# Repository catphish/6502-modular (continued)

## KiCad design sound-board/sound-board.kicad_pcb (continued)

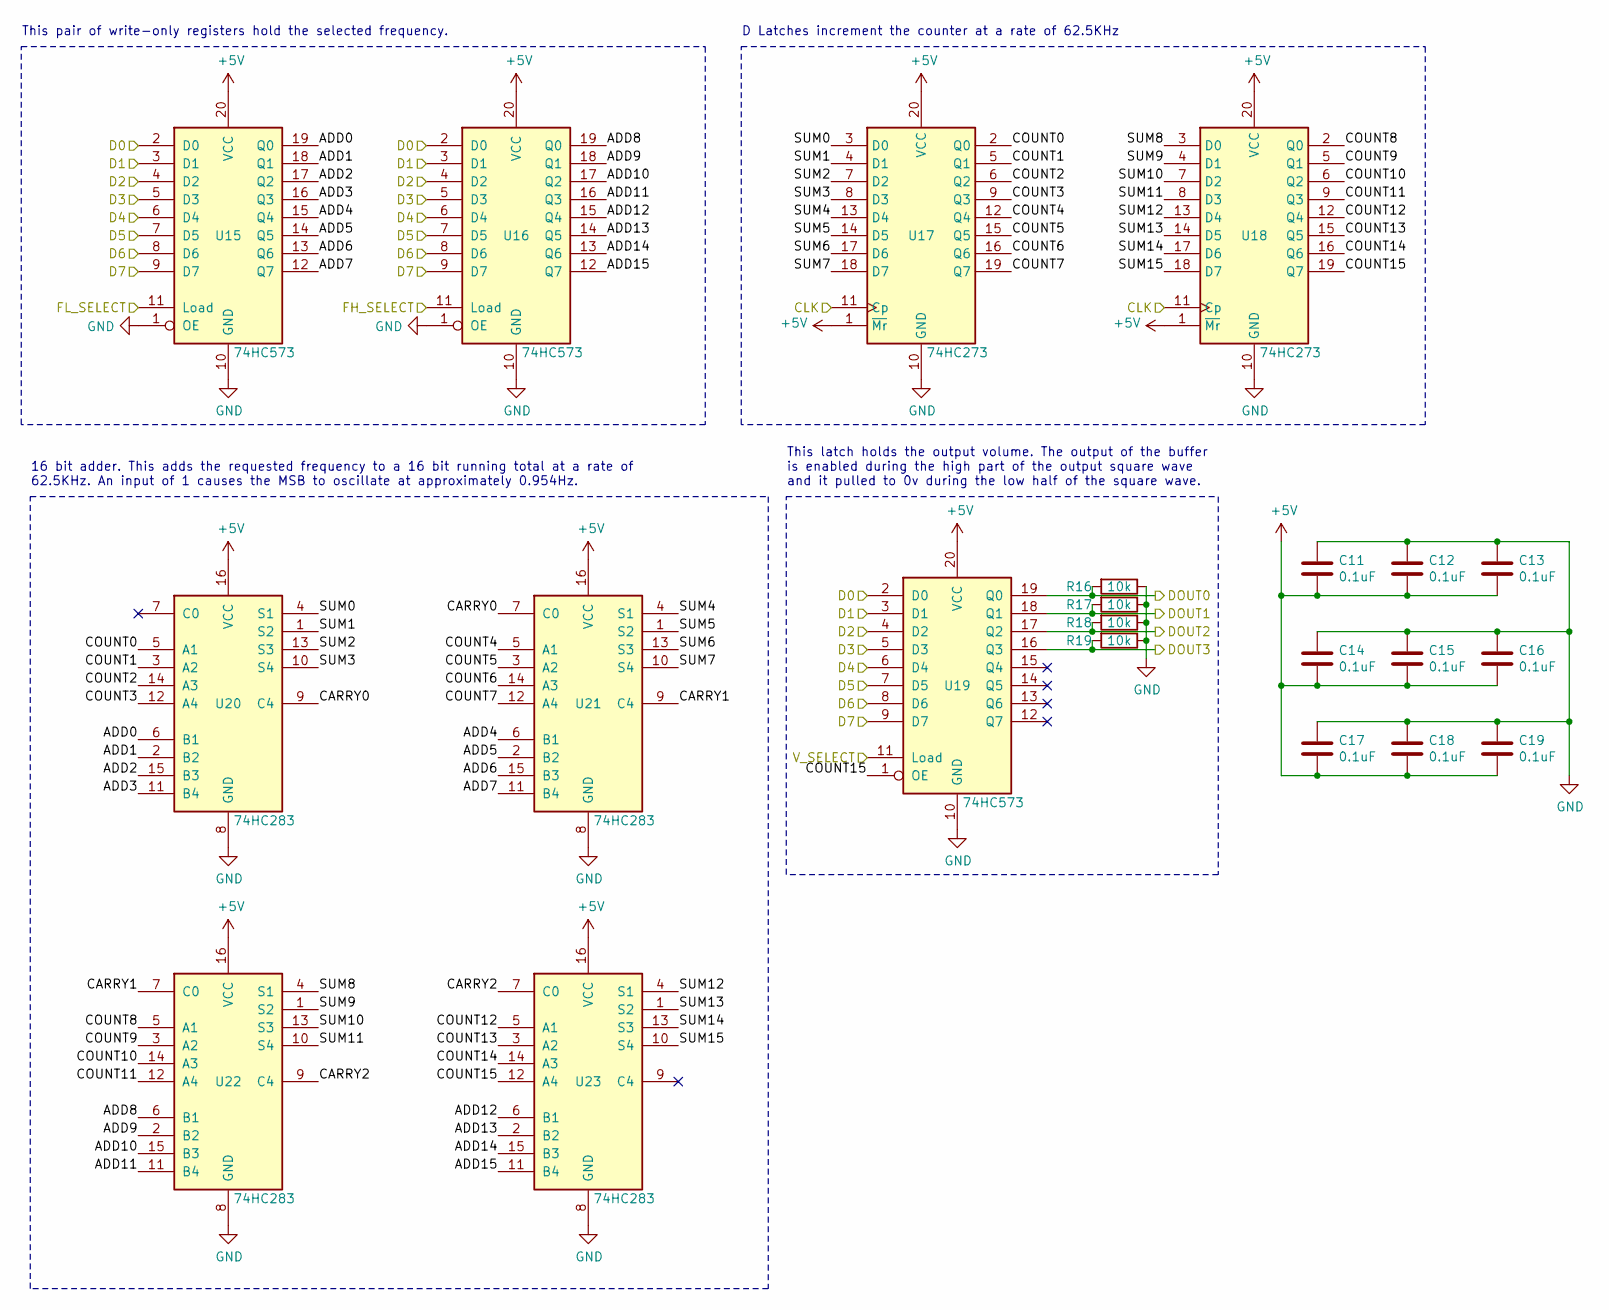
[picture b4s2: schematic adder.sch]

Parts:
C2, C3, C4, C5, C6, C7, C8, C9, C10: 0.1uF; C_Disc_D6.0mm_W2.5mm_P5.00mm
R16, R17, R18, R19: 10k; R_Axial_DIN0207_L6.3mm_D2.5mm_P10.16mm_Horizontal
U6, U7, U19: 74HC573; DIP-20_W7.62mm_Socket
U8, U9: 74HC273; DIP-20_W7.62mm_Socket
U11, U12, U13, U14: 74HC283; DIP-16_W7.62mm_Socket

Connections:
+5V: C2.2, C3.2, C4.2, C5.2, C6.2, C7.2, C8.2, C9.2, C10.2, U6.20 (VCC), U7.20 (VCC), U8.1 (~Mr), U8.20 (VCC), U9.1 (~Mr), U9.20 (VCC), U11.16 (VCC), U12.16 (VCC), U13.16 (VCC), U14.16 (VCC), U19.20 (VCC); also elsewhere on the board
/Wave Generator A/ADD0: U6.19 (Q0), U11.6 (B1)
/Wave Generator A/ADD1: U6.18 (Q1), U11.2 (B2)
/Wave Generator A/ADD2: U6.17 (Q2), U11.15 (B3)
/Wave Generator A/ADD3: U6.16 (Q3), U11.11 (B4)
/Wave Generator A/ADD4: U6.15 (Q4), U12.6 (B1)
/Wave Generator A/ADD5: U6.14 (Q5), U12.2 (B2)
/Wave Generator A/ADD6: U6.13 (Q6), U12.15 (B3)
/Wave Generator A/ADD7: U6.12 (Q7), U12.11 (B4)
/Wave Generator A/ADD8: U7.19 (Q0), U13.6 (B1)
/Wave Generator A/ADD9: U7.18 (Q1), U13.2 (B2)
/Wave Generator A/ADD10: U7.17 (Q2), U13.15 (B3)
/Wave Generator A/ADD11: U7.16 (Q3), U13.11 (B4)
/Wave Generator A/ADD12: U7.15 (Q4), U14.6 (B1)
/Wave Generator A/ADD13: U7.14 (Q5), U14.2 (B2)
/Wave Generator A/ADD14: U7.13 (Q6), U14.15 (B3)
/Wave Generator A/ADD15: U7.12 (Q7), U14.11 (B4)
/Wave Generator A/CARRY0: U11.9 (C4), U12.7 (C0)
/Wave Generator A/CARRY1: U12.9 (C4), U13.7 (C0)
/Wave Generator A/CARRY2: U13.9 (C4), U14.7 (C0)
/Wave Generator A/COUNT0: U8.2 (Q0), U11.5 (A1)
/Wave Generator A/COUNT1: U8.5 (Q1), U11.3 (A2)
/Wave Generator A/COUNT2: U8.6 (Q2), U11.14 (A3)
/Wave Generator A/COUNT3: U8.9 (Q3), U11.12 (A4)
/Wave Generator A/COUNT4: U8.12 (Q4), U12.5 (A1)
/Wave Generator A/COUNT5: U8.15 (Q5), U12.3 (A2)
/Wave Generator A/COUNT6: U8.16 (Q6), U12.14 (A3)
/Wave Generator A/COUNT7: U8.19 (Q7), U12.12 (A4)
/Wave Generator A/COUNT8: U9.2 (Q0), U13.5 (A1)
/Wave Generator A/COUNT9: U9.5 (Q1), U13.3 (A2)
/Wave Generator A/COUNT10: U9.6 (Q2), U13.14 (A3)
/Wave Generator A/COUNT11: U9.9 (Q3), U13.12 (A4)
/Wave Generator A/COUNT12: U9.12 (Q4), U14.5 (A1)
/Wave Generator A/COUNT13: U9.15 (Q5), U14.3 (A2)
/Wave Generator A/COUNT14: U9.16 (Q6), U14.14 (A3)
/Wave Generator A/SUM0: U8.3 (D0), U11.4 (S1)
/Wave Generator A/SUM1: U8.4 (D1), U11.1 (S2)
/Wave Generator A/SUM2: U8.7 (D2), U11.13 (S3)
/Wave Generator A/SUM3: U8.8 (D3), U11.10 (S4)
/Wave Generator A/SUM4: U8.13 (D4), U12.4 (S1)
/Wave Generator A/SUM5: U8.14 (D5), U12.1 (S2)
/Wave Generator A/SUM6: U8.17 (D6), U12.13 (S3)
/Wave Generator A/SUM7: U8.18 (D7), U12.10 (S4)
/Wave Generator A/SUM8: U9.3 (D0), U13.4 (S1)
/Wave Generator A/SUM9: U9.4 (D1), U13.1 (S2)
/Wave Generator A/SUM10: U9.7 (D2), U13.13 (S3)
/Wave Generator A/SUM11: U9.8 (D3), U13.10 (S4)
/Wave Generator A/SUM12: U9.13 (D4), U14.4 (S1)
/Wave Generator A/SUM13: U9.14 (D5), U14.1 (S2)
/Wave Generator A/SUM14: U9.17 (D6), U14.13 (S3)
/Wave Generator A/SUM15: U9.18 (D7), U14.10 (S4)
CLK_62K5: U8.11 (Cp), U9.11 (Cp); also elsewhere on the board
D0: U6.2 (D0), U7.2 (D0), U19.2 (D0); also elsewhere on the board
D1: U6.3 (D1), U7.3 (D1), U19.3 (D1); also elsewhere on the board
D2: U6.4 (D2), U7.4 (D2), U19.4 (D2); also elsewhere on the board
D3: U6.5 (D3), U7.5 (D3), U19.5 (D3); also elsewhere on the board
D4: U6.6 (D4), U7.6 (D4), U19.6 (D4); also elsewhere on the board
D5: U6.7 (D5), U7.7 (D5), U19.7 (D5); also elsewhere on the board
D6: U6.8 (D6), U7.8 (D6), U19.8 (D6); also elsewhere on the board
D7: U6.9 (D7), U7.9 (D7), U19.9 (D7); also elsewhere on the board
DIGITAL_B_0: R16.2, U19.19 (Q0); also elsewhere on the board
DIGITAL_B_1: R17.2, U19.18 (Q1); also elsewhere on the board
DIGITAL_B_2: R18.2, U19.17 (Q2); also elsewhere on the board
DIGITAL_B_3: R19.2, U19.16 (Q3); also elsewhere on the board
FA_H_SELECT: U7.11 (Load); also elsewhere on the board
FA_L_SELECT: U6.11 (Load); also elsewhere on the board
GND: C2.1, C3.1, C4.1, C5.1, C6.1, C7.1, C8.1, C9.1, C10.1, R16.1, R17.1, R18.1, R19.1, U6.1 (OE), U6.10 (GND), U7.1 (OE), U7.10 (GND), U8.10 (GND), U9.10 (GND), U11.8 (GND), U12.8 (GND), U13.8 (GND), U14.8 (GND), U19.10 (GND); also elsewhere on the board
VB_SELECT: U19.11 (Load); also elsewhere on the board

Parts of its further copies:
C11, C12, C13, C14, C15, C16, C17, C18, C19: 0.1uF; C_Disc_D6.0mm_W2.5mm_P5.00mm
R12, R13, R14, R15: 10k; R_Axial_DIN0207_L6.3mm_D2.5mm_P10.16mm_Horizontal
U10, U15, U16: 74HC573; DIP-20_W7.62mm_Socket
U17, U18: 74HC273; DIP-20_W7.62mm_Socket
U20, U21, U22, U23: 74HC283; DIP-16_W7.62mm_Socket

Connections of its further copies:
+5V: C11.2, C12.2, C13.2, C14.2, C15.2, C16.2, C17.2, C18.2, C19.2, U10.20 (VCC), U15.20 (VCC), U16.20 (VCC), U17.1 (~Mr), U17.20 (VCC), U18.1 (~Mr), U18.20 (VCC), U20.16 (VCC), U21.16 (VCC), U22.16 (VCC), U23.16 (VCC); also elsewhere on the board
/Wave Generator B/ADD0: U15.19 (Q0), U20.6 (B1)
/Wave Generator B/ADD1: U15.18 (Q1), U20.2 (B2)
/Wave Generator B/ADD2: U15.17 (Q2), U20.15 (B3)
/Wave Generator B/ADD3: U15.16 (Q3), U20.11 (B4)
/Wave Generator B/ADD4: U15.15 (Q4), U21.6 (B1)
/Wave Generator B/ADD5: U15.14 (Q5), U21.2 (B2)
/Wave Generator B/ADD6: U15.13 (Q6), U21.15 (B3)
/Wave Generator B/ADD7: U15.12 (Q7), U21.11 (B4)
/Wave Generator B/ADD8: U16.19 (Q0), U22.6 (B1)
/Wave Generator B/ADD9: U16.18 (Q1), U22.2 (B2)
/Wave Generator B/ADD10: U16.17 (Q2), U22.15 (B3)
/Wave Generator B/ADD11: U16.16 (Q3), U22.11 (B4)
/Wave Generator B/ADD12: U16.15 (Q4), U23.6 (B1)
/Wave Generator B/ADD13: U16.14 (Q5), U23.2 (B2)
/Wave Generator B/ADD14: U16.13 (Q6), U23.15 (B3)
/Wave Generator B/ADD15: U16.12 (Q7), U23.11 (B4)
/Wave Generator B/CARRY0: U20.9 (C4), U21.7 (C0)
/Wave Generator B/CARRY1: U21.9 (C4), U22.7 (C0)
/Wave Generator B/CARRY2: U22.9 (C4), U23.7 (C0)
/Wave Generator B/COUNT0: U17.2 (Q0), U20.5 (A1)
/Wave Generator B/COUNT1: U17.5 (Q1), U20.3 (A2)
/Wave Generator B/COUNT2: U17.6 (Q2), U20.14 (A3)
/Wave Generator B/COUNT3: U17.9 (Q3), U20.12 (A4)
/Wave Generator B/COUNT4: U17.12 (Q4), U21.5 (A1)
/Wave Generator B/COUNT5: U17.15 (Q5), U21.3 (A2)
/Wave Generator B/COUNT6: U17.16 (Q6), U21.14 (A3)
/Wave Generator B/COUNT7: U17.19 (Q7), U21.12 (A4)
/Wave Generator B/COUNT8: U18.2 (Q0), U22.5 (A1)
/Wave Generator B/COUNT9: U18.5 (Q1), U22.3 (A2)
/Wave Generator B/COUNT10: U18.6 (Q2), U22.14 (A3)
/Wave Generator B/COUNT11: U18.9 (Q3), U22.12 (A4)
/Wave Generator B/COUNT12: U18.12 (Q4), U23.5 (A1)
/Wave Generator B/COUNT13: U18.15 (Q5), U23.3 (A2)
/Wave Generator B/COUNT14: U18.16 (Q6), U23.14 (A3)
/Wave Generator B/SUM0: U17.3 (D0), U20.4 (S1)
/Wave Generator B/SUM1: U17.4 (D1), U20.1 (S2)
/Wave Generator B/SUM2: U17.7 (D2), U20.13 (S3)
/Wave Generator B/SUM3: U17.8 (D3), U20.10 (S4)
/Wave Generator B/SUM4: U17.13 (D4), U21.4 (S1)
/Wave Generator B/SUM5: U17.14 (D5), U21.1 (S2)
/Wave Generator B/SUM6: U17.17 (D6), U21.13 (S3)
/Wave Generator B/SUM7: U17.18 (D7), U21.10 (S4)
/Wave Generator B/SUM8: U18.3 (D0), U22.4 (S1)
/Wave Generator B/SUM9: U18.4 (D1), U22.1 (S2)
/Wave Generator B/SUM10: U18.7 (D2), U22.13 (S3)
/Wave Generator B/SUM11: U18.8 (D3), U22.10 (S4)
/Wave Generator B/SUM12: U18.13 (D4), U23.4 (S1)
/Wave Generator B/SUM13: U18.14 (D5), U23.1 (S2)
/Wave Generator B/SUM14: U18.17 (D6), U23.13 (S3)
/Wave Generator B/SUM15: U18.18 (D7), U23.10 (S4)
CLK_62K5: U17.11 (Cp), U18.11 (Cp); also elsewhere on the board
D0: U10.2 (D0), U15.2 (D0), U16.2 (D0); also elsewhere on the board
D1: U10.3 (D1), U15.3 (D1), U16.3 (D1); also elsewhere on the board
D2: U10.4 (D2), U15.4 (D2), U16.4 (D2); also elsewhere on the board
D3: U10.5 (D3), U15.5 (D3), U16.5 (D3); also elsewhere on the board
D4: U10.6 (D4), U15.6 (D4), U16.6 (D4); also elsewhere on the board
D5: U10.7 (D5), U15.7 (D5), U16.7 (D5); also elsewhere on the board
D6: U10.8 (D6), U15.8 (D6), U16.8 (D6); also elsewhere on the board
D7: U10.9 (D7), U15.9 (D7), U16.9 (D7); also elsewhere on the board
DIGITAL_A_0: R12.2, U10.19 (Q0); also elsewhere on the board
DIGITAL_A_1: R13.2, U10.18 (Q1); also elsewhere on the board
DIGITAL_A_2: R14.2, U10.17 (Q2); also elsewhere on the board
DIGITAL_A_3: R15.2, U10.16 (Q3); also elsewhere on the board
FB_H_SELECT: U16.11 (Load); also elsewhere on the board
FB_L_SELECT: U15.11 (Load); also elsewhere on the board
GND: C11.1, C12.1, C13.1, C14.1, C15.1, C16.1, C17.1, C18.1, C19.1, R12.1, R13.1, R14.1, R15.1, U10.10 (GND), U15.1 (OE), U15.10 (GND), U16.1 (OE), U16.10 (GND), U17.10 (GND), U18.10 (GND), U20.8 (GND), U21.8 (GND), U22.8 (GND), U23.8 (GND); also elsewhere on the board
VA_SELECT: U10.11 (Load); also elsewhere on the board

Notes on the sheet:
This pair of write-only registers hold the selected frequency.
16 bit adder. This adds the requested frequency to a 16 bit running total at a rate of 62.5KHz. An input of 1 causes the MSB to oscillate at approximately 0.954Hz.
D Latches increment the counter at a rate of 62.5KHz
This latch holds the output volume. The output of the buffer is enabled during the high part of the output square wave and it pulled to 0v during the low half of the square wave.

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
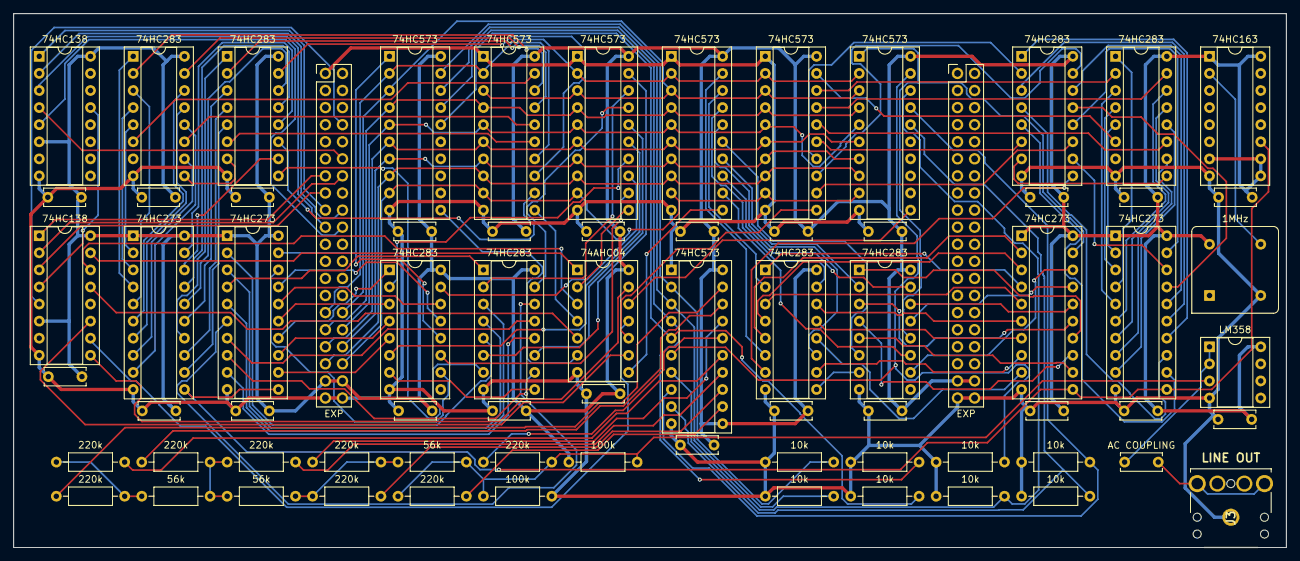
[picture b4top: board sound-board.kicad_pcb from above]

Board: 2 copper layers, 189.2 x 79.4 mm, 74 parts (0 on the bottom side), 158 nets.

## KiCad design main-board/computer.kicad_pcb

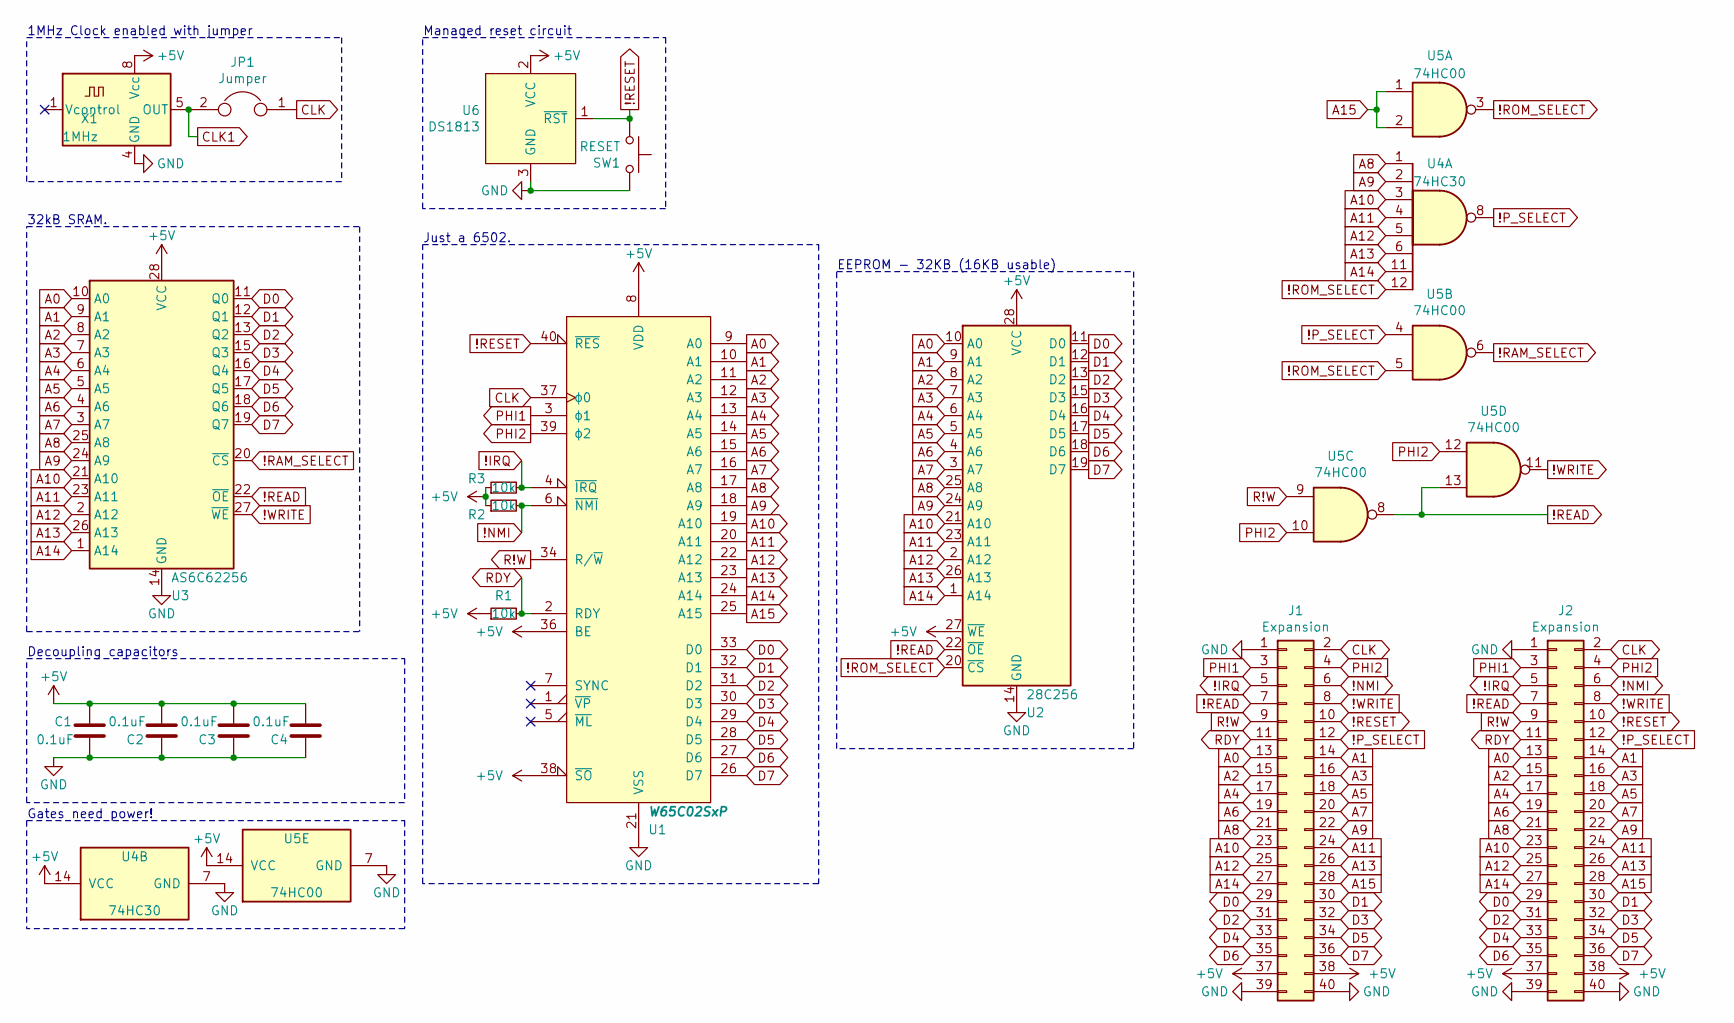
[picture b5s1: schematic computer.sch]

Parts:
C1, C2, C3, C4: 0.1uF; C_Disc_D6.0mm_W2.5mm_P5.00mm
J1, J2: Expansion; PinHeader_2x20_P2.54mm_Vertical
JP1: Jumper; PinHeader_1x02_P2.54mm_Horizontal
R1, R2, R3: 10k; R_Axial_DIN0207_L6.3mm_D2.5mm_P10.16mm_Horizontal
SW1: RESET; SW_PUSH_6mm
U1: W65C02SxP; DIP-40_W15.24mm_Socket
U2: 28C256; DIP-28_W15.24mm_Socket
U3: AS6C62256; DIP-28_W15.24mm_Socket
U4: 74HC30; DIP-14_W7.62mm_Socket
U5: 74HC00; DIP-14_W7.62mm_Socket
U6: DS1813; TO-92_Inline_Horizontal1
X1: 1MHz; Oscillator_DIP-8

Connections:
!IRQ: J1.5, J2.5, R3.2, U1.4 (~IRQ)
!NMI: J1.6, J2.6, R2.2, U1.6 (~NMI)
!P_SELECT: J1.12, J2.12, U4.8, U5.4
!RAM_SELECT: U3.20 (~CS), U5.6
!READ: J1.7, J2.7, U2.22 (~OE), U3.22 (~OE), U5.8, U5.13
!RESET: J1.10, J2.10, SW1.1, U1.40 (~RES), U6.1 (~RST)
!ROM_SELECT: U2.20 (~CS), U4.12, U5.3, U5.5
!WRITE: J1.8, J2.8, U3.27 (~WE), U5.11
+5V: C1.1, C2.2, C3.2, C4.2, J1.37, J1.38, J2.37, J2.38, R1.1, R2.1, R3.1, U1.8 (VDD), U1.36 (BE), U1.38 (~SO), U2.27 (~WE), U2.28 (VCC), U3.28 (VCC), U4.14 (VCC), U5.14 (VCC), U6.2 (VCC), X1.8 (Vcc)
A0: J1.13, J2.13, U1.9 (A0), U2.10 (A0), U3.10 (A0)
A1: J1.14, J2.14, U1.10 (A1), U2.9 (A1), U3.9 (A1)
A2: J1.15, J2.15, U1.11 (A2), U2.8 (A2), U3.8 (A2)
A3: J1.16, J2.16, U1.12 (A3), U2.7 (A3), U3.7 (A3)
A4: J1.17, J2.17, U1.13 (A4), U2.6 (A4), U3.6 (A4)
A5: J1.18, J2.18, U1.14 (A5), U2.5 (A5), U3.5 (A5)
A6: J1.19, J2.19, U1.15 (A6), U2.4 (A6), U3.4 (A6)
A7: J1.20, J2.20, U1.16 (A7), U2.3 (A7), U3.3 (A7)
A8: J1.21, J2.21, U1.17 (A8), U2.25 (A8), U3.25 (A8), U4.1
A9: J1.22, J2.22, U1.18 (A9), U2.24 (A9), U3.24 (A9), U4.2
A10: J1.23, J2.23, U1.19 (A10), U2.21 (A10), U3.21 (A10), U4.3
A11: J1.24, J2.24, U1.20 (A11), U2.23 (A11), U3.23 (A11), U4.4
A12: J1.25, J2.25, U1.22 (A12), U2.2 (A12), U3.2 (A12), U4.5
A13: J1.26, J2.26, U1.23 (A13), U2.26 (A13), U3.26 (A13), U4.6
A14: J1.27, J2.27, U1.24 (A14), U2.1 (A14), U3.1 (A14), U4.11
A15: J1.28, J2.28, U1.25 (A15), U5.1, U5.2
CLK: J1.2, J2.2, JP1.1, U1.37 (ϕ0)
CLK1: JP1.2, X1.5 (OUT)
D0: J1.29, J2.29, U1.33 (D0), U2.11 (D0), U3.11 (Q0)
D1: J1.30, J2.30, U1.32 (D1), U2.12 (D1), U3.12 (Q1)
D2: J1.31, J2.31, U1.31 (D2), U2.13 (D2), U3.13 (Q2)
D3: J1.32, J2.32, U1.30 (D3), U2.15 (D3), U3.15 (Q3)
D4: J1.33, J2.33, U1.29 (D4), U2.16 (D4), U3.16 (Q4)
D5: J1.34, J2.34, U1.28 (D5), U2.17 (D5), U3.17 (Q5)
D6: J1.35, J2.35, U1.27 (D6), U2.18 (D6), U3.18 (Q6)
D7: J1.36, J2.36, U1.26 (D7), U2.19 (D7), U3.19 (Q7)
GND: C1.2, C2.1, C3.1, C4.1, J1.1, J1.39, J1.40, J2.1, J2.39, J2.40, SW1.2, U1.21 (VSS), U2.14 (GND), U3.14 (GND), U4.7 (GND), U5.7 (GND), U6.3 (GND), X1.4 (GND)
PHI1: J1.3, J2.3, U1.3 (ϕ1)
PHI2: J1.4, J2.4, U1.39 (ϕ2), U5.10, U5.12
R!W: J1.9, J2.9, U1.34 (R/~W), U5.9
RDY: J1.11, J2.11, R1.2, U1.2 (RDY)

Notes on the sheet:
32kB SRAM.
Gates need power!
1MHz Clock enabled with jumper
Decoupling capacitors
Just a 6502.
EEPROM - 32KB (16KB usable)
Managed reset circuit

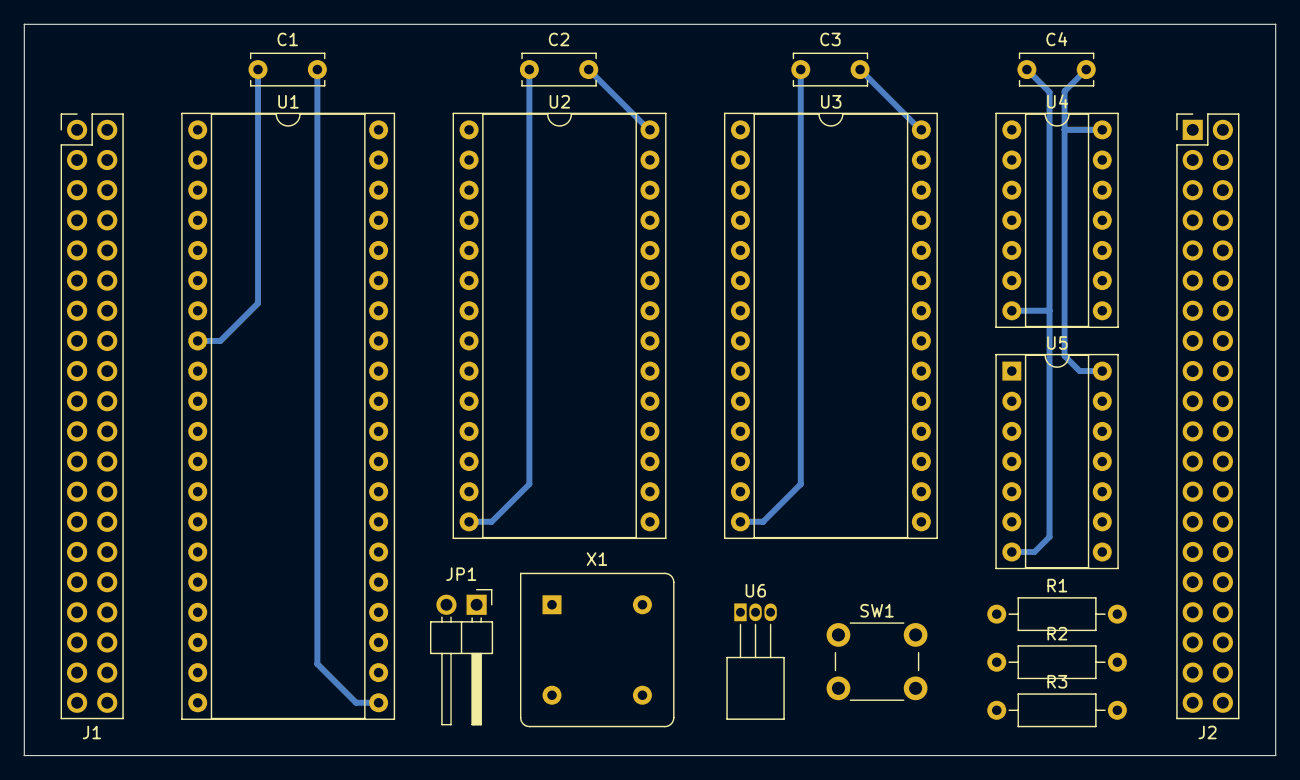
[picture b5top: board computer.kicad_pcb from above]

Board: 2 copper layers, 105.4 x 61.6 mm, 18 parts (0 on the bottom side), 40 nets.

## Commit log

2020-11-29 Remove not yet required IC from schematic
2020-11-29 Tidying
2020-11-30 Fix EEPROM description
2020-11-30 Tidy schematic
2020-12-04 More tidying up
2020-12-04 Add more boards, rearrange files
2020-12-05 begin vga design
2020-12-06 remove vga board, finish other boards
2020-12-18 Add VGA (not complete)
2020-12-21 More on VGA
2020-12-22 Add VGA socket, fix routing errors on CPU board
2020-12-22 Fix IO board routing errors
2020-12-23 Integtrate IO into mail board, begion VGA layout
2020-12-24 More on layouts
2020-12-25 Revert "More on layouts"
    This reverts commit 3fc7c4d1a32f245eaa0a26aebed00be081417dbd.
2020-12-25 Revert "Integtrate IO into mail board, begion VGA layout"
    This reverts commit 15baf3f71fbe492a9e0b6e5b5ec863db56e31855.
2020-12-25 Redesign CPU and IO boards
2020-12-26 Finish designing and routing new CPU and IO boards
2020-12-26 Design new VGA board
2020-12-26 Finish and route VGA board
2020-12-27 Rename main board files
2020-12-28 Add sound board
2020-12-28 Replot gerbers
2020-12-28 route sound board
2021-01-09 remove old peripheral boards, begn new vga design
2021-01-09 continue new vga
2021-01-10 more vga board routing
2021-01-16 reroute main board and IO board again
